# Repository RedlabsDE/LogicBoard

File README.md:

# LogicBoard 027/00

Basic logic gates circuit for kids

Order PCB here: https://aisler.net/p/EYQMMKUZ

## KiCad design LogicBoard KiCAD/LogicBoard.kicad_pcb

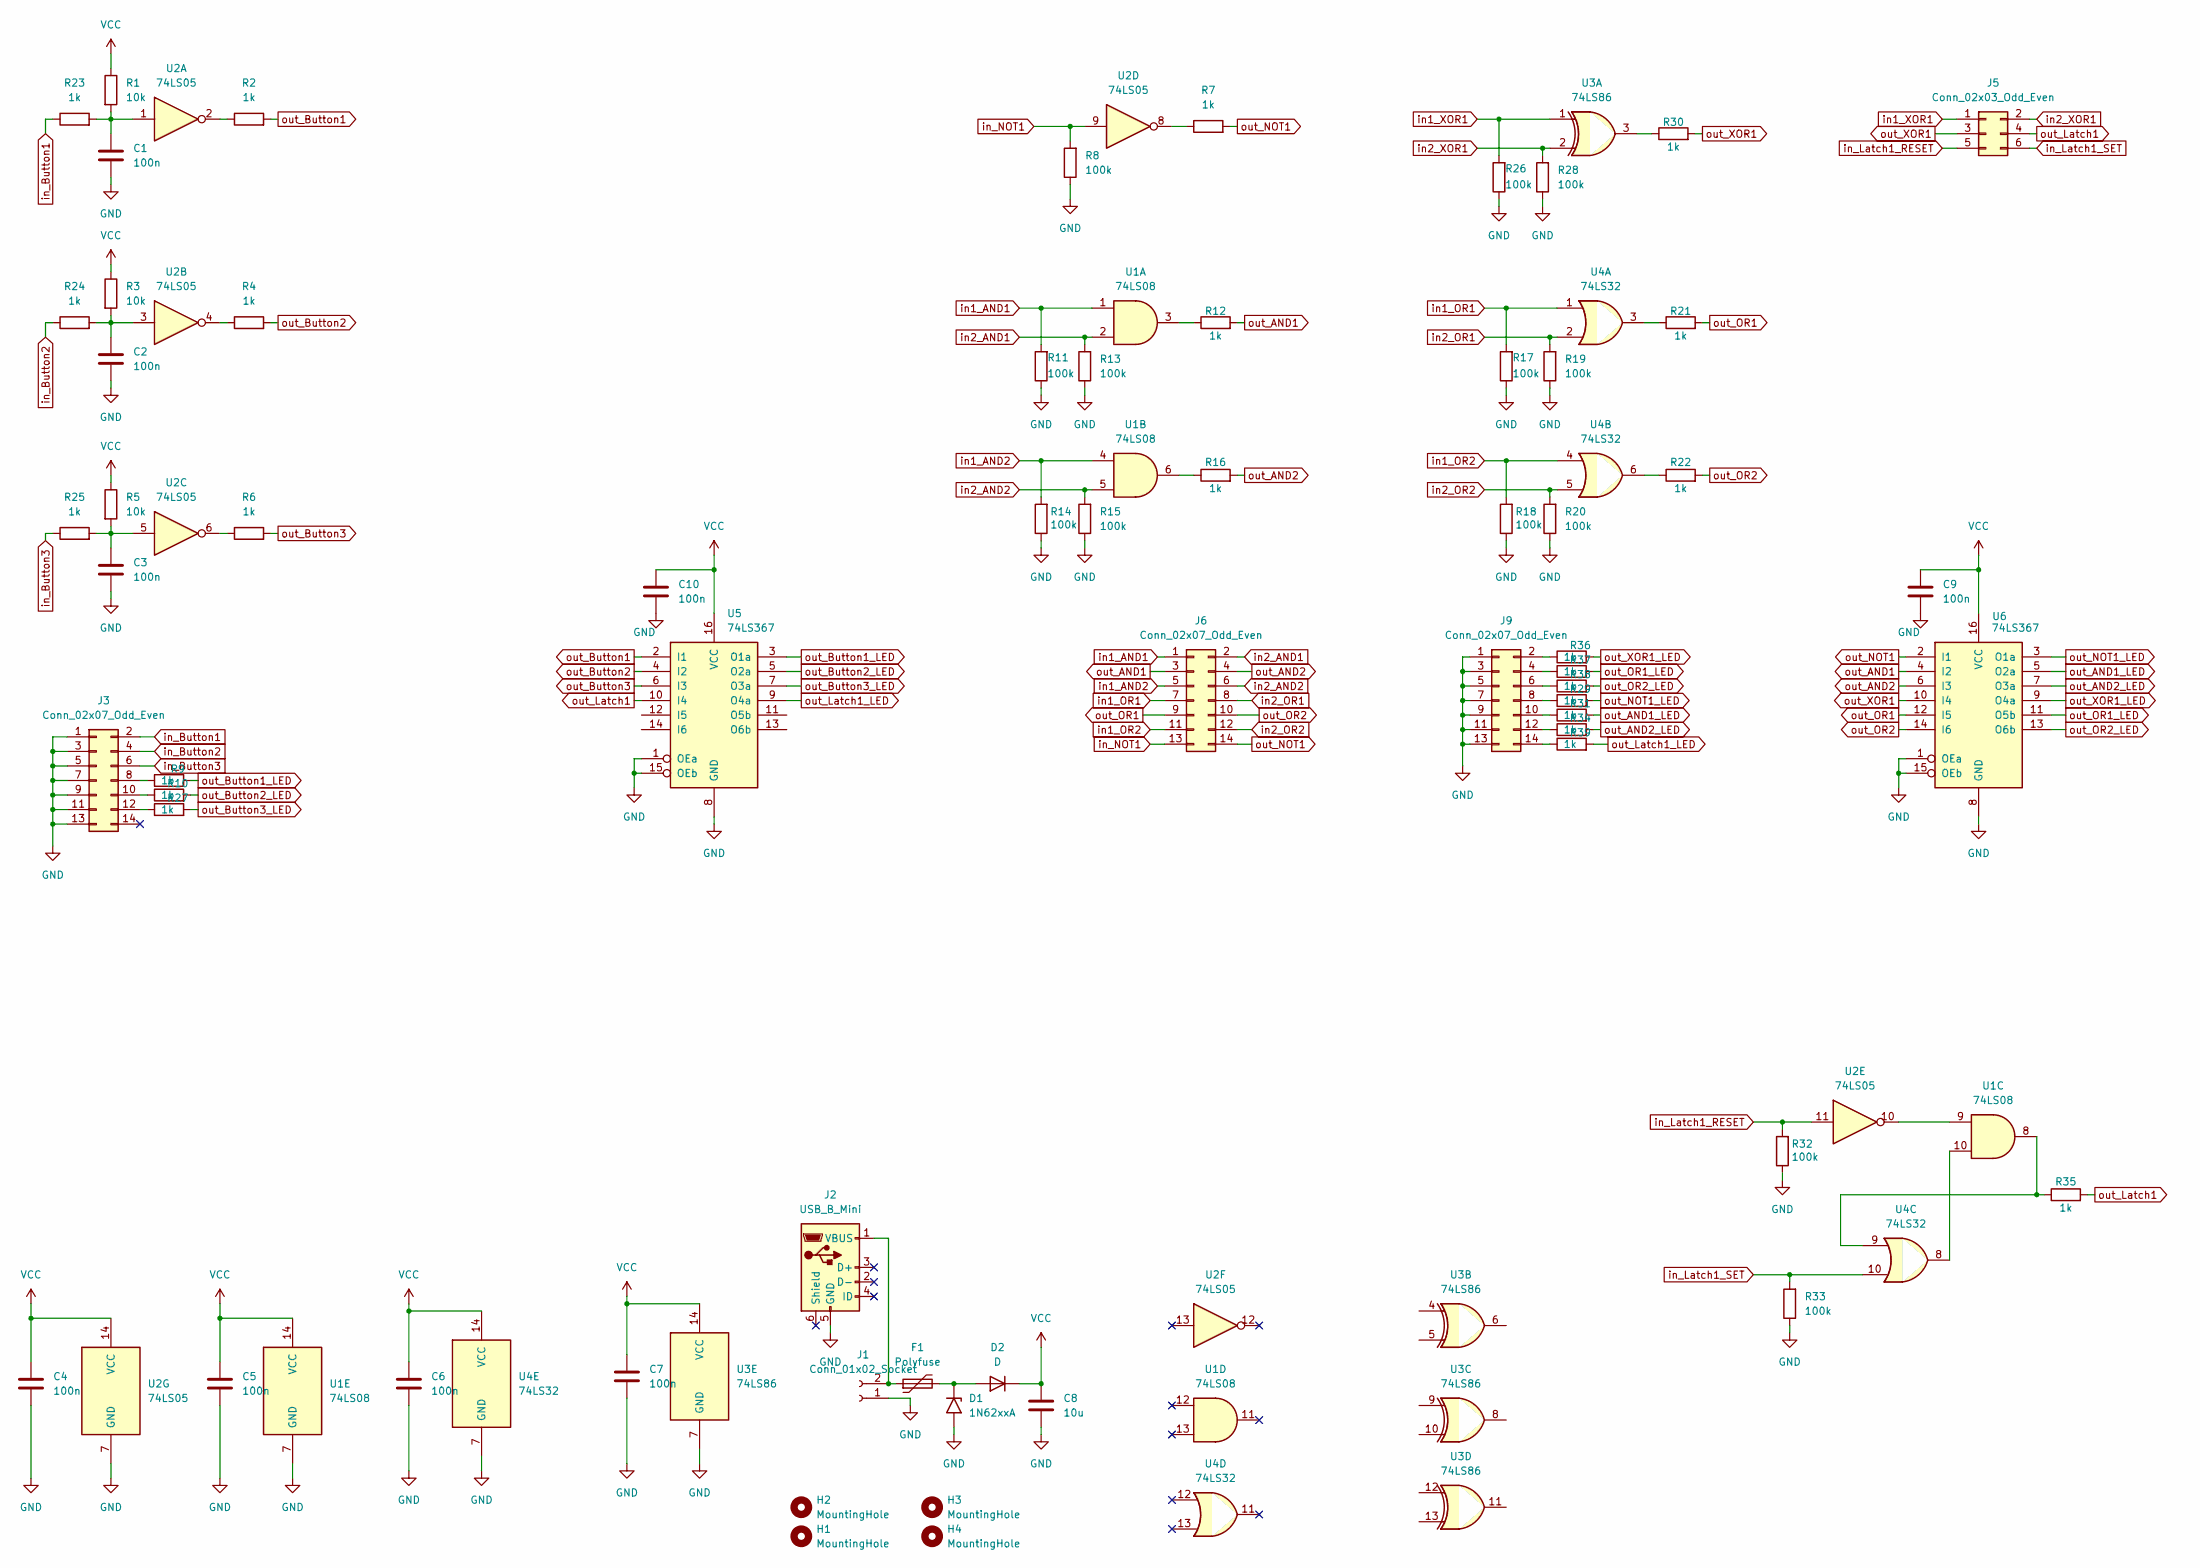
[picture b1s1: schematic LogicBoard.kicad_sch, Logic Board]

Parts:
C1, C2, C3, C4, C5, C6, C7, C9, C10: 100n; C_Disc_D3.0mm_W2.0mm_P2.50mm
C8: 10u; C_Radial_D6.3mm_H11.0mm_P2.50mm
D1: 1N62xxA; D_DO-201AE_P3.81mm_Vertical_AnodeUp
D2: D; D_DO-201AE_P3.81mm_Vertical_AnodeUp
F1: Polyfuse; C_Disc_D3.0mm_W2.0mm_P2.50mm
H1, H2, H3, H4: MountingHole; MountingHole_2.5mm
J1: Conn_01x02_Socket; JST_NV_B02P-NV_1x02_P5.00mm_Vertical
J2: USB_B_Mini; USB_Mini-B_Wuerth_65100516121_Horizontal
J3, J6, J9: Conn_02x07_Odd_Even; PinHeader_2x07_P2.54mm_Wannenstecker_WSL14
J5: Conn_02x03_Odd_Even; PinHeader_2x03_Wannenstecker_WSL6G
R1, R3, R5: 10k; R_Axial_DIN0207_L6.3mm_D2.5mm_P10.16mm_Horizontal
R2, R4, R6, R7, R9, R10, R12, R16, R21, R22, R23, R24, R25, R27, R29, R30, R31, R34, R35, R36, R37, R38, R39: 1k; R_Axial_DIN0207_L6.3mm_D2.5mm_P10.16mm_Horizontal
R8, R11, R13, R14, R15, R17, R18, R19, R20, R26, R28, R32, R33: 100k; R_Axial_DIN0207_L6.3mm_D2.5mm_P10.16mm_Horizontal
U1: 74LS08; DIP-14_W7.62mm_LongPads
U2: 74LS05; DIP-14_W7.62mm_LongPads
U3: 74LS86; DIP-14_W7.62mm_LongPads
U4: 74LS32; DIP-14_W7.62mm_LongPads
U5, U6: 74LS367; DIP-16_W7.62mm_LongPads

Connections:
GND: C1.2, C2.2, C3.2, C4.2, C5.2, C6.2, C7.2, C8.2, C9.2, C10.2, D1.2 (A2), J1.1, J2.5 (GND), J3.1, J3.3, J3.5, J3.7, J3.9, J3.11, J3.13, J9.1, J9.3, J9.5, J9.7, J9.9, J9.11, J9.13, R8.1, R11.1, R13.1, R14.1, R15.1, R17.1, R18.1, R19.1, R20.1, R26.1, R28.1, R32.1, R33.1, U1.7 (GND), U2.7 (GND), U3.7 (GND), U4.7 (GND), U5.1 (OEa), U5.8 (GND), U5.15 (OEb), U6.1 (OEa), U6.8 (GND), U6.15 (OEb)
unnamed: C1.1, R1.2, R23.2, U2.1
unnamed: C2.1, R3.2, R24.2, U2.3
unnamed: C3.1, R5.2, R25.2, U2.5
unnamed: D1.1 (A1), D2.2 (A), F1.2
unnamed: F1.1, J1.2, J2.1 (VBUS)
unnamed: J3.8, R9.1
unnamed: J3.10, R10.1
unnamed: J3.12, R27.1
unnamed: J9.2, R36.1
unnamed: J9.4, R37.1
unnamed: J9.6, R38.1
unnamed: J9.8, R29.1
unnamed: J9.10, R31.1
unnamed: J9.12, R34.1
unnamed: J9.14, R39.1
unnamed: R2.1, U2.2
unnamed: R4.1, U2.4
unnamed: R6.1, U2.6
unnamed: R7.1, U2.8
unnamed: R12.1, U1.3
unnamed: R16.1, U1.6
unnamed: R21.1, U4.3
unnamed: R22.1, U4.6
unnamed: R30.1, U3.3
unnamed: R35.1, U1.8, U4.9
unnamed: U1.9, U2.10
unnamed: U1.10, U4.8
VCC: C4.1, C5.1, C6.1, C7.1, C8.1, C9.1, C10.1, D2.1 (K), R1.1, R3.1, R5.1, U1.14 (VCC), U2.14 (VCC), U3.14 (VCC), U4.14 (VCC), U5.16 (VCC), U6.16 (VCC)
in1_AND1: J6.1, R11.2, U1.1
in1_AND2: J6.5, R14.2, U1.4
in1_OR1: J6.7, R17.2, U4.1
in1_OR2: J6.11, R18.2, U4.4
in1_XOR1: J5.1, R26.2, U3.1
in2_AND1: J6.2, R13.2, U1.2
in2_AND2: J6.6, R15.2, U1.5
in2_OR1: J6.8, R19.2, U4.2
in2_OR2: J6.12, R20.2, U4.5
in2_XOR1: J5.2, R28.2, U3.2
in_Button1: J3.2, R23.1
in_Button2: J3.4, R24.1
in_Button3: J3.6, R25.1
in_Latch1_RESET: J5.5, R32.2, U2.11
in_Latch1_SET: J5.6, R33.2, U4.10
in_NOT1: J6.13, R8.2, U2.9
out_AND1: J6.3, R12.2, U6.4 (I2)
out_AND1_LED: R31.2, U6.5 (O2a)
out_AND2: J6.4, R16.2, U6.6 (I3)
out_AND2_LED: R34.2, U6.7 (O3a)
out_Button1: R2.2, U5.2 (I1)
out_Button1_LED: R9.2, U5.3 (O1a)
out_Button2: R4.2, U5.4 (I2)
out_Button2_LED: R10.2, U5.5 (O2a)
out_Button3: R6.2, U5.6 (I3)
out_Button3_LED: R27.2, U5.7 (O3a)
out_Latch1: J5.4, R35.2, U5.10 (I4)
out_Latch1_LED: R39.2, U5.9 (O4a)
out_NOT1: J6.14, R7.2, U6.2 (I1)
out_NOT1_LED: R29.2, U6.3 (O1a)
out_OR1: J6.9, R21.2, U6.12 (I5)
out_OR1_LED: R37.2, U6.11 (O5b)
out_OR2: J6.10, R22.2, U6.14 (I6)
out_OR2_LED: R38.2, U6.13 (O6b)
out_XOR1: J5.3, R30.2, U6.10 (I4)
out_XOR1_LED: R36.2, U6.9 (O4a)

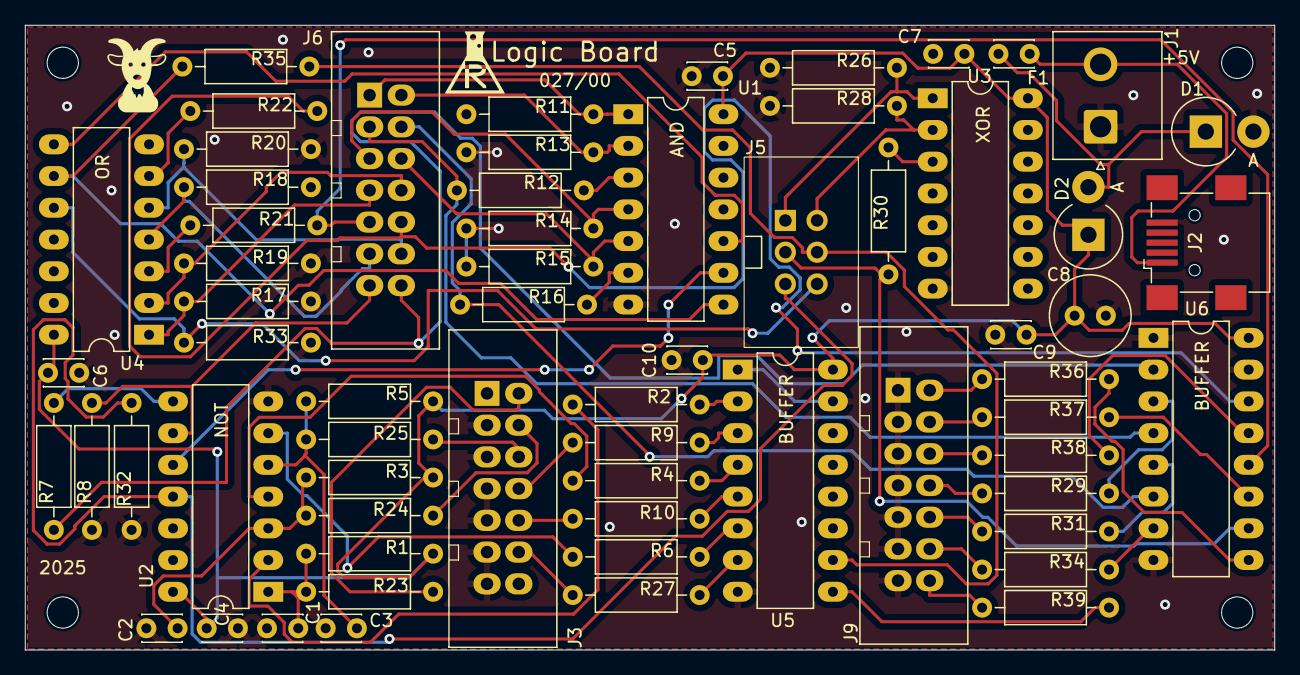
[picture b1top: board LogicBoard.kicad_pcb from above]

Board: 2 copper layers, 100.0 x 50.0 mm, 68 parts (0 on the bottom side), 65 nets.
